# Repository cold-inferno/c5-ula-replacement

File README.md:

# C5 ULA replacement — firmware V1203

A replacement for the **Ferranti ULA (5G014)** control chip of the **Sinclair C5**, built on
**["ULA replacement" by Philipp Bank (cypax)](https://www.cypax.net/projects/ula/)** (2010–2011).
A small ATmega board plugs into the original 28-pin ULA socket in the pod and takes over the
LED displays, motor relay, battery/current/temperature monitoring and the buzzer.

This repository continues that project with new firmware, a fixed bootloader, support for the
**ATmega328P**, a **browser-based configurator** for any OS, and the board files in KiCad format.

> **Status:** bootloader V1044 and firmware V1202 were tested on the bench on an ATmega328P board
> (flashed, read back byte-identical, logging and serial verified). Firmware V1203 builds and passes
> the checks but hasn't been run on hardware yet. Not yet road-tested in a C5.
> The ATmega88 builds compile and pass the same checks but haven't been run on hardware.

## What's new compared to cypax V1172

**Pedal assist (pedelec)**
- Speed uses the wheel size you configure (the original always used 1280 mm).
- Hysteresis at both speed limits and a minimum relay switching time: no more relay chatter.
- Max speed `0` = no upper cut-off (motor assists at any speed while pedalling).
  A pedelec without the 25 km/h cut-off is not road-legal as a bicycle in the EU.
- Pedal sensor debounce; no phantom "pedalling" right after power-on.

**Battery (LiFePO4)**
- LiFePO4 profile (default, 12.8 V / 4 cells): LED bar and cut-off use the *resting* voltage
  (motor off for ~3 s), low-battery warning, cut-off if the voltage collapses under load.
  The original lead-acid behaviour is still available as a build option.

**Display and logging**
- Left LED bar shows **speed** (1 LED per 5 km/h) while the motor button is released,
  motor current while it is pressed.
- Clear **fault codes** (V1203): one LED per kind of fault, slow flash = warning, fast flash =
  error, buzzer in the same rhythm. All codes are in [CHEATSHEET.md](CHEATSHEET.md).
- Optional **ride log** (off by default): reset-cause counters, an event log of warnings and
  errors, and a 60-second **black box** saved after an unexpected restart.

**Robustness**
- Stall protection (V1203): high current while the wheel doesn't turn cuts the motor until the
  button is released; the 140 A cut no longer retries forever.
- Bootloader V1044: switches the watchdog off at start (the original could hang in a reset
  loop after a watchdog reset until the C5 was switched off), supports 128-byte flash pages
  and hands the reset cause to the firmware.
- Interrupt-safe timer access, VREF underflow fix, `printf` replaced (frees ~1.4 KB).
- Builds with today's avr-gcc for **ATmega88** (original) and **ATmega328P** (pin-compatible).

**Tools**
- Browser configurator (Web Serial, or Web Bluetooth with an HM-10 / AT-09 module): live data,
  settings, firmware upload (USB only), ride log. Refuses firmware built for the other chip.
- Python tools for macOS/Linux: CRC (replaces `crc_calc.exe`), monitor/upload, log decoder.
- Host unit tests for the motor relay and stall logic.

## Repository layout

| Path | Contents |
|---|---|
| `*.c`, `*.h`, `makefile` | firmware |
| `CHEATSHEET.md` | all LED, buzzer, serial and ride-log codes |
| `bootloader/` | bootloader |
| `release/` | ready-to-flash files per chip (`_m88`, `_m328p`) and EEPROM defaults |
| `configurator/` | browser configurator (`index.html`) and macOS launcher |
| `tools/` | `build-all.sh`, `fwcrc.py`, `ula_monitor.py`, `ula_log.py` |
| `test/` | host unit tests (`make -C test`) |
| `hardware/` | original Eagle files, EAGLE XML export, KiCad project, Gerber zip |

## Hardware

- Board: 49 × 19 mm, 2 layers. `hardware/gerbers/ULA_Replacement_gerbers.zip` can be ordered
  as-is from common PCB makers (2 layers, 1.6 mm).
- Chip: **ATmega88** (as designed) or **ATmega328P** (same package and pinout, more memory).
  The schematic symbol is labelled `MEGA8-AI`; the firmware has always been for the ATmega88.
- 16 MHz crystal, 0805 resistors/capacitors, 2 × 14-pin strips for the ULA socket,
  10-pin ISP header, 4-pin serial header (+5V, GND, RXD, TXD), 4-pin pedal/wheel sensor header.

**C5 modifications** (control box, see the
[cypax installation chapter](https://www.cypax.net/projects/ula/?l=en#installation) for photos):
the original ULA set the current-sense gain with an internal DAC, which the ATmega lacks.
- Solder a 47 kΩ resistor between pins 7 and 3 of the LM358 op-amp.
- Remove R5.
- Disconnect the wire at X9 pin 8 ("CS Emitter"); it becomes the optional fan output.

Pedal assist needs two reed switches with magnets (wheel and pedal) on the sensor header.
Without them, switch pedal assist off in the configurator: the motor then runs whenever the
handlebar button is pressed. The button always powers the motor relay, so the firmware can
only *allow* the motor, never force it on.

## Flashing

You need a USBasp (or any ISP programmer) on the 10-pin header for the fuses and the bootloader,
and a 5 V USB-serial adapter (FT232/CP2102) on the 4-pin header for everything else.
**Power the board from one source only** (USBasp jumper on **5 V** on the bench, or the C5).

| | ATmega328P | ATmega88 |
|---|---|---|
| lfuse | `0xF7` (full-swing crystal) | `0xEF` |
| hfuse | `0xD2` (boot 2 KB at 0x7800, EEPROM kept on erase) | `0xDF` |
| efuse | `0xFC` (brown-out 4.3 V) | `0xFA` (boot 1 KB at 0x1C00) |

```bash
cd release
# ATmega328P
avrdude -c usbasp -p m328p -U lfuse:w:0xF7:m -U hfuse:w:0xD2:m -U efuse:w:0xFC:m
avrdude -c usbasp -p m328p -e -U flash:w:bootloader_V1044_m328p.hex:i
# then upload the firmware over serial (configurator or tools/ula_monitor.py upload),
# or directly with the programmer:
avrdude -c usbasp -p m328p -D -U flash:w:ULA_firmware_V1203_LiFePO4_m328p.hex:i -U eeprom:w:ULA_eeprom_defaults.eep:i
```

The 328P brown-out level of 4.3 V keeps the chip off below that voltage, so a programmer
jumper left on 3.3 V shows up as a silent board.

## Configurator

Open `configurator/index.html` in **Chrome or Edge** (Web Serial; Safari and Firefox don't
support it). It must be served from `localhost` or https: on macOS double-click
`configurator/start-configurator.command`, elsewhere run
`python3 -m http.server 8765 --directory configurator` and open <http://localhost:8765>.
The **Demo** button simulates a C5.

**Bluetooth:** with an HM-10 / AT-09 serial module on the 4-pin header, *Connect Bluetooth* gives
live data and settings without a cable (Chrome/Edge, Chrome on Android, Bluefy on iPhone).
Entering configuration mode over Bluetooth depends on the module reconnecting within the
bootloader's 2 seconds; if it misses, just try again. Firmware upload is USB only.

The original Windows `Uploader.exe` is no longer supported: it only accepts bootloader V1042.
Use this configurator or `tools/ula_monitor.py` instead.

- **Live data:** speed, cadence, battery (live and resting), current, relay, button,
  temperature, warnings and a mirror of the pod LEDs.
- **Settings:** click *Enter configuration mode*, then switch the C5 off and on (the bootloader
  listens for 2 s after power-on). Values are written and read back to verify.
- **Firmware update** and **Ride log** (read, chart, CSV export, clear) also run through the bootloader.
  The upload checks that the file matches the chip on the board (`_m88` / `_m328p`).

## Settings (EEPROM)

| Offset | Size | Setting | Default |
|---|---|---|---|
| 0 | 1 | pedal assist (pedelec) on/off | on |
| 1 | 2 | wheel circumference, mm (configurator limit 1500) | 1280 |
| 3 | 2 | max speed, 0.1 km/h (0 = no limit, V1200+) | 250 |
| 5 | 2 | min speed, 0.1 km/h | 30 |
| 7 | 2 | fan switch-on temperature, °C | 45 |
| 9 | 1 | magnets on the wheel | 1 |
| 10 | 1 | magnets on the pedals | 1 |
| 11 | 1 | ride log (1 = on, V1202+) | off |

All values are little-endian. The ride log uses offsets 16 and up (see `ridelog.h`).

## Serial interface

9600 baud, 8N1, 5 V TTL. At start-up the firmware prints its version, CRC and battery profile (up to V1202 also the
settings; read those in configuration mode now), then four status lines per second:

```
#DIST|SPEED|RPM|TIMEOUT|SWITCH|TEMP|VOLT|VREF|CURR|ENA|COND|TIME|REST|
```

The first twelve fields are as in cypax V1172 (raw ADC values; battery volts ≈ `(VOLT+32)/48`);
`REST` (resting battery voltage, ADC) was added in V1200.
The bootloader protocol is unchanged from V1042 (`e v g r w f s x`, see `bootloader/bootload.c`).

## Building

```bash
brew tap osx-cross/avr && brew install osx-cross/avr/avr-gcc@14 avrdude
tools/build-all.sh          # firmware + bootloader for both chips into release/
make -C test                # host unit tests
make MCU=atmega328p         # a single firmware build (ula_repl_crc.hex)
```

`build-all.sh` stops on compiler warnings, a wrong firmware CRC, an oversized bootloader, or
black-box RAM that the bootloader could overwrite. The firmware CRC (checked by the firmware's
self-test) is embedded by `tools/fwcrc.py`.

## Command-line tools

```bash
python3 tools/ula_monitor.py listen            # decode the live data (sends nothing)
python3 tools/ula_monitor.py settings          # read settings via the bootloader
python3 tools/ula_monitor.py upload release/ULA_firmware_V1203_LiFePO4_m328p.hex
python3 tools/ula_log.py usbasp m328p          # read and decode the ride log with a USBasp
python3 tools/ula_log.py serial --csv bb.csv   # same over serial, black box as CSV
```

## Known limitations

- Stall protection (V1203) uses guessed limits (about 80 A for 3 s without a wheel pulse, see
  `pedelec.h`) that still need tuning on the road. Without a wheel sensor only the
  "third 140 A cut in a row" rule protects a blocked motor.
- The temperature table assumes a sensor of about 4 kΩ at room temperature; check that *Live data*
  shows a plausible motor temperature before relying on it.
- A rare timing race when reading the pedal sensor can drop the motor for about 0.5 s; assist
  continues for up to 2 s after you stop pedalling (by design).
- The bootloader starts the firmware without verifying it (the firmware checks itself while
  running), and stays in configuration mode until *Start C5* or a power cycle.
- Wheels above 1820 mm overflow the speed sensor's bounce filter.
- Ride log: a quick off-and-on is recorded as a brown-out.

## Credits and license

Original design, firmware, bootloader and documentation: **Philipp Bank (cypax.net)**.
Background on the original ULA: the c5alive.co.uk documents referenced on the cypax page.

Code and hardware: **CC BY-NC-SA 3.0**; documentation: **CC BY-SA 3.0** — see
[LICENSE.md](LICENSE.md). No commercial use without the original author's permission.
No warranty: this controls a vehicle's motor; use at your own risk.

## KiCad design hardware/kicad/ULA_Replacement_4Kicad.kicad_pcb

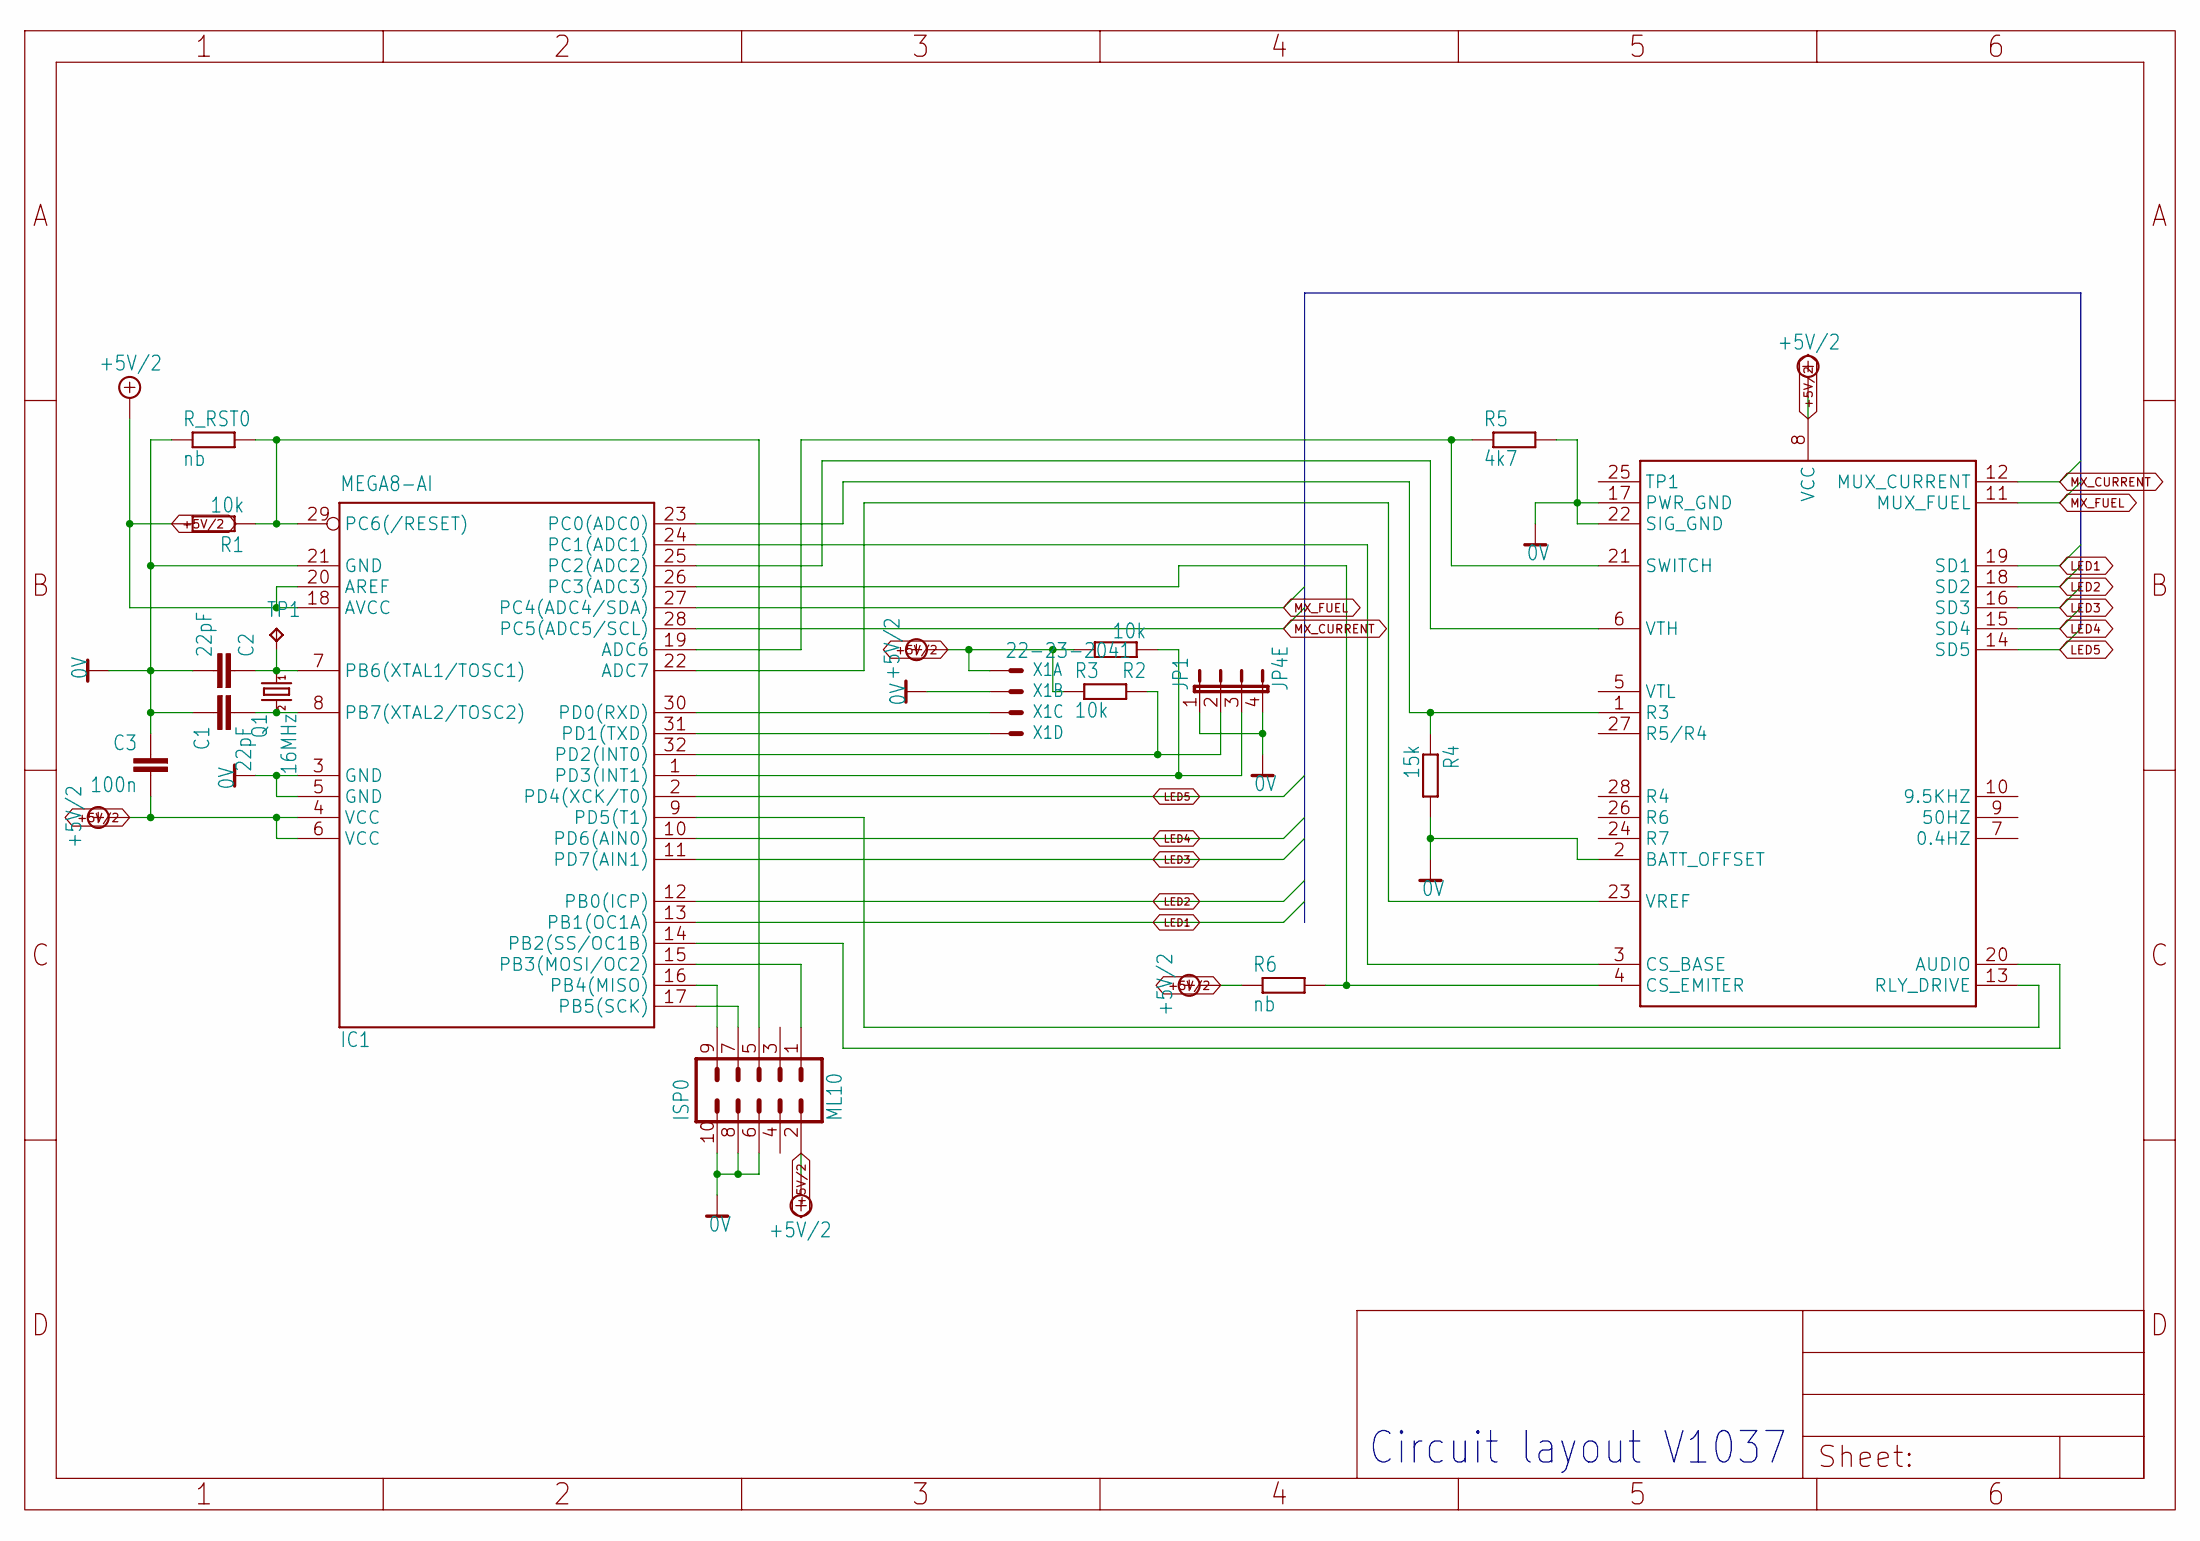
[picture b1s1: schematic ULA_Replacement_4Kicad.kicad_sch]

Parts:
C1, C2: 22pF; C0805
C3: 100n; C0805
IC1: MEGA8-AI; TQFP32-08
ISP0: ML10
JP1: JP4E; JP4
Q1: 16MHz; HC49_S
R1, R2, R3: 10k; M0805
R4: 15k; M0805
R5: 4k7; M0805
R6: nb; M0805
R_RST0: nb; 0204V
TP1: TPB1,27; B1,27
U$1: C5_ULA
X1: 22-23-2041

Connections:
+5V/2: C3.2, IC1.4 (VCC), IC1.6 (VCC), IC1.18 (AVCC), IC1.20 (AREF), ISP0.2, R1.2, R2.2, R3.1, R6.1, U$1.8 (VCC), X1.1
/RESET: IC1.29 (PC6(/RESET)), ISP0.5, R1.1, R_RST0.2
AUDIO: IC1.14 (PB2(SS/OC1B)), U$1.20 (AUDIO)
CS_BASE: IC1.24 (PC1(ADC1)), U$1.3 (CS_BASE)
CS_EMITER: IC1.26 (PC3(ADC3)), R6.2, U$1.4 (CS_EMITER)
GND: C1.1, C2.2, C3.1, IC1.3 (GND), IC1.5 (GND), IC1.21 (GND), ISP0.6, ISP0.8, ISP0.10, JP1.1, JP1.4, R4.2, R5.2, R_RST0.1, U$1.2 (BATT_OFFSET), U$1.17 (PWR_GND), U$1.22 (SIG_GND), X1.2
INT0: IC1.32 (PD2(INT0)), JP1.2, R3.2
INT1: IC1.1 (PD3(INT1)), JP1.3, R2.1
LED1: IC1.13 (PB1(OC1A)), U$1.19 (SD1)
LED2: IC1.12 (PB0(ICP)), U$1.18 (SD2)
LED3: IC1.11 (PD7(AIN1)), U$1.16 (SD3)
LED4: IC1.10 (PD6(AIN0)), U$1.15 (SD4)
LED5: IC1.2 (PD4(XCK/T0)), U$1.14 (SD5)
MISO: IC1.16 (PB4(MISO)), ISP0.9
MOSI: IC1.15 (PB3(MOSI/OC2)), ISP0.1
MX_CURRENT: IC1.28 (PC5(ADC5/SCL)), U$1.12 (MUX_CURRENT)
MX_FUEL: IC1.27 (PC4(ADC4/SDA)), U$1.11 (MUX_FUEL)
R3: IC1.23 (PC0(ADC0)), R4.1, U$1.1 (R3)
RLY_DRIVE: IC1.9 (PD5(T1)), U$1.13 (RLY_DRIVE)
RXD: IC1.30 (PD0(RXD)), X1.3
SCK: IC1.17 (PB5(SCK)), ISP0.7
SWITCH: IC1.19 (ADC6), R5.1, U$1.21 (SWITCH)
TXD: IC1.31 (PD1(TXD)), X1.4
VREF: IC1.22 (ADC7), U$1.23 (VREF)
VTH: IC1.25 (PC2(ADC2)), U$1.6 (VTH)
XTAL1: C2.1, IC1.7 (PB6(XTAL1/TOSC1)), Q1.1, TP1.TP
XTAL2: C1.2, IC1.8 (PB7(XTAL2/TOSC2)), Q1.2

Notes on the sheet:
Circuit layout V1037

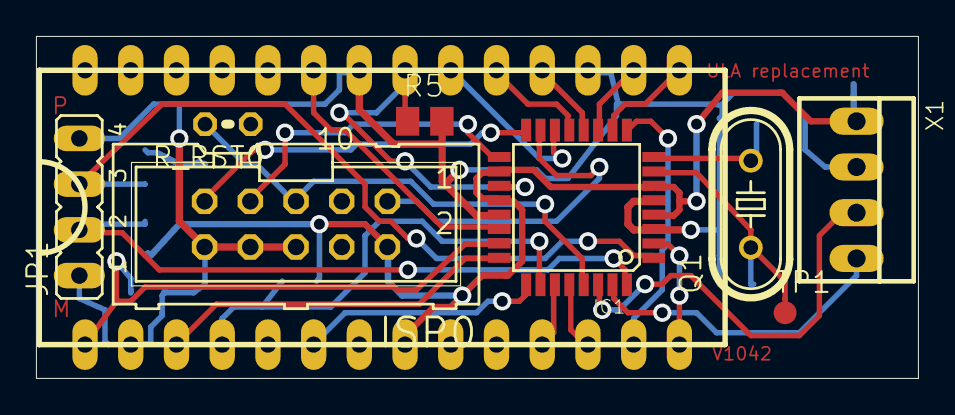
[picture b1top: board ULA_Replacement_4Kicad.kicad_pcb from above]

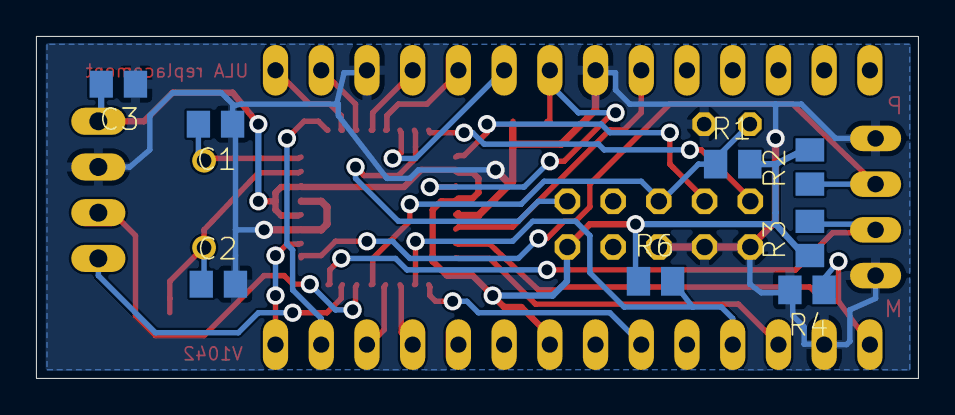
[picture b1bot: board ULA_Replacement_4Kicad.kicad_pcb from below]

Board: 2 copper layers, 49.0 x 19.0 mm, 17 parts (8 on the bottom side), 27 nets.

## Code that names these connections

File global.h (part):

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/* RS232 RXD */
#define RXD_PORT            PORTD
#define RXD_DDR             DDRD
#define RXD_BIT             PD0

/* RS232 TXD */
#define TXD_PORT            PORTD
#define TXD_DDR             DDRD
#define TXD_BIT             PD1

/* LEDs */
#define LED1_PORT           PORTB
#define LED1_DDR            DDRB
#define LED1_BIT            PB1

#define LED2_PORT           PORTB
#define LED2_DDR            DDRB
#define LED2_BIT            PB0

#define LED3_PORT           PORTD
#define LED3_DDR            DDRD
#define LED3_BIT            PD7

#define LED4_PORT           PORTD
#define LED4_DDR            DDRD
#define LED4_BIT            PD6

#define LED5_PORT           PORTD
#define LED5_DDR            DDRD
#define LED5_BIT            PD4

/* Multiplex */
#define MUX_VOLT_PORT       PORTC
#define MUX_VOLT_DDR        DDRC
#define MUX_VOLT_BIT        PC4

#define MUX_CURR_PORT       PORTC
#define MUX_CURR_DDR        DDRC
#define MUX_CURR_BIT        PC5

/* Speaker */
#define SPEAKER_PORT        PORTB
#define SPEAKER_DDR         DDRB
#define SPEAKER_BIT         PB2

/* Motor relay */
#define RELAY_PORT          PORTD
#define RELAY_DDR           DDRD
#define RELAY_BIT           PD5

/* Fan */
#define FAN_PORT            PORTC
#define FAN_DDR             DDRC
#define FAN_BIT             PC3

/* Tacho sensor */
#define INT0_PORT           PORTD
#define INT0_DDR            DDRD
#define INT0_BIT            PD2

/* Pedal sensor */
#define INT1_PORT           PORTD
#define INT1_DDR            DDRD
#define INT1_BIT            PD3

/* VREF */
#define VREF_PORT           PORTC
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/* CSBASE (current) */
#define CSBASE_PORT         PORTC
#define CSBASE_DDR          DDRC
#define CSBASE_BIT          PC1

/* R3 (voltage) */
#define R3_PORT             PORTC
#define R3_DDR              DDRC
#define R3_BIT              PC0

/* VTH (temperature) */
#define VTH_PORT            PORTC
#define VTH_DDR             DDRC
#define VTH_BIT             PC2

/* SWITCH */
#define SWITCH_PORT         PORTC
#define SWITCH_DDR          DDRC
#define SWITCH_BIT          6

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#define LOW_BYTE(x)  ((UINT8)  x)

/** @brief Macro function to turn LED1 on                                     */
#define LED1_ON()       LED1_PORT &= ~(1U << LED1_BIT);
/** @brief Macro function to turn LED1 off                                    */
#define LED1_OFF()      LED1_PORT |=  (1U << LED1_BIT);

/** @brief Macro function to turn LED2 on                                     */
#define LED2_ON()       LED2_PORT &= ~(1U << LED2_BIT);
/** @brief Macro function to turn LED2 off                                    */
#define LED2_OFF()      LED2_PORT |=  (1U << LED2_BIT);

/** @brief Macro function to turn LED3 on                                     */
#define LED3_ON()       LED3_PORT &= ~(1U << LED3_BIT);
/** @brief Macro function to turn LED3 off                                    */
#define LED3_OFF()      LED3_PORT |=  (1U << LED3_BIT);

/** @brief Macro function to turn LED4 on                                     */
#define LED4_ON()       LED4_PORT &= ~(1U << LED4_BIT);
/** @brief Macro function to turn LED4 off                                    */
#define LED4_OFF()      LED4_PORT |=  (1U << LED4_BIT);

/** @brief Macro function to turn LED5 on                                     */
#define LED5_ON()       LED5_PORT &= ~(1U << LED5_BIT);
/** @brief Macro function to turn LED5 off                                    */
#define LED5_OFF()      LED5_PORT |=  (1U << LED5_BIT);

/** @brief Short macro to turn all LEDs on (used for flashing)                */
#define ALL_LEDS_ON()   {LED1_ON(); LED2_ON(); LED3_ON(); \
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

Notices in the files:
global.h:
@copyright Creative Commons by-nc-sa 3.0
(http://creativecommons.org/licenses/by-nc-sa/3.0/)
